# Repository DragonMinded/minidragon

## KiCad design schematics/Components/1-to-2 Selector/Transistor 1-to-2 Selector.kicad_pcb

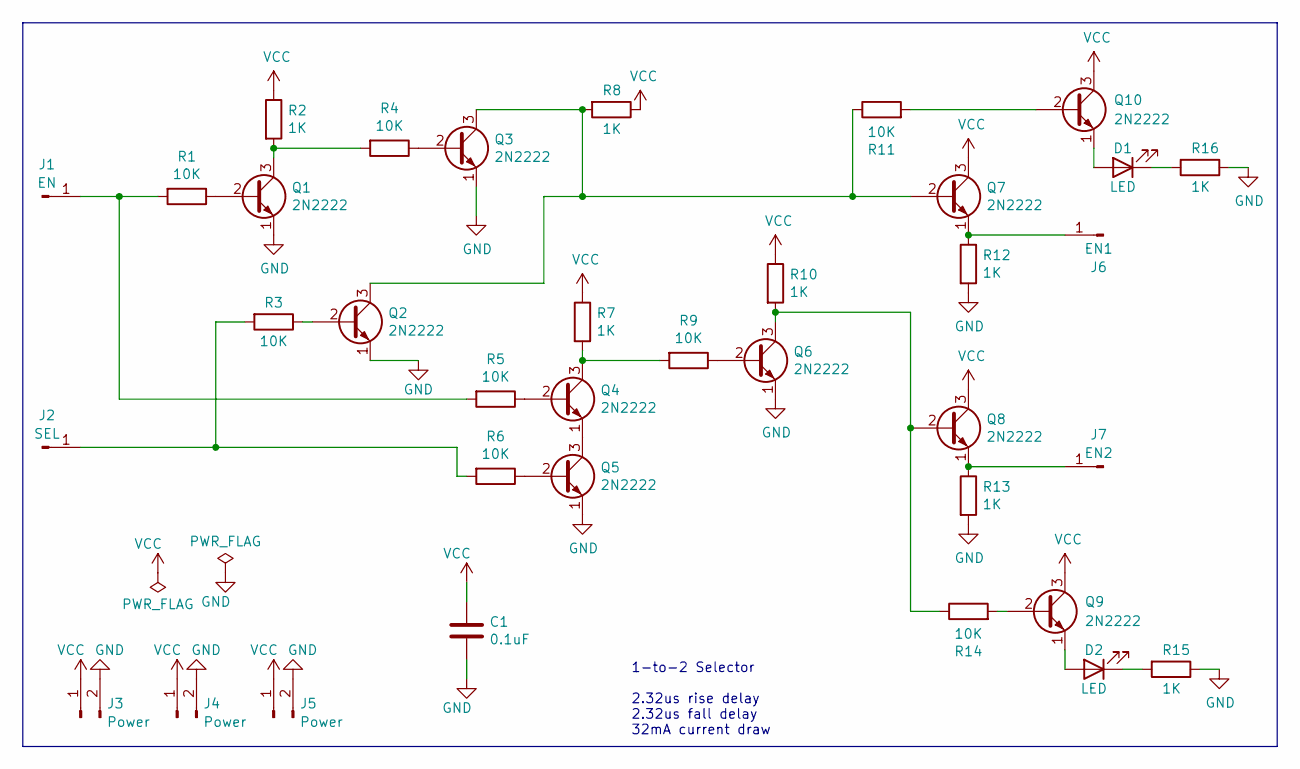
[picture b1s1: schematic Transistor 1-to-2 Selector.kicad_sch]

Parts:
C1: 0.1uF; C_Disc_D4.3mm_W1.9mm_P5.00mm
D1, D2: LED; LED_D5.0mm
J1: EN; PinHeader_1x01_P2.54mm_Vertical
J2: SEL; PinHeader_1x01_P2.54mm_Vertical
J3, J4, J5: Power; PinHeader_1x02_P2.54mm_Vertical
J6: EN1; PinHeader_1x01_P2.54mm_Vertical
J7: EN2; PinHeader_1x01_P2.54mm_Vertical
Q1, Q2, Q3, Q4, Q5, Q6, Q7, Q8, Q9, Q10: 2N2222; TO-92_Inline
R1, R3, R4, R5, R6, R9, R11, R14: 10K; R_Axial_DIN0309_L9.0mm_D3.2mm_P12.70mm_Horizontal
R2, R7, R8, R10, R12, R13, R15, R16: 1K; R_Axial_DIN0309_L9.0mm_D3.2mm_P12.70mm_Horizontal

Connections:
GND: C1.2, J3.2, J4.2, J5.2, Q1.1 (E), Q2.1 (E), Q3.1 (E), Q5.1 (E), Q6.1 (E), R12.2, R13.2, R15.1, R16.1
unnamed: D1.2 (A), Q10.1 (E)
unnamed: D1.1 (K), R16.2
unnamed: D2.2 (A), Q9.1 (E)
unnamed: D2.1 (K), R15.2
unnamed: J1.1, R1.2, R5.2
unnamed: J2.1, R3.2, R6.2
unnamed: J6.1, Q7.1 (E), R12.1
unnamed: J7.1, Q8.1 (E), R13.1
unnamed: Q1.2 (B), R1.1
unnamed: Q1.3 (C), R2.2, R4.2
unnamed: Q2.2 (B), R3.1
unnamed: Q2.3 (C), Q3.3 (C), Q7.2 (B), R8.2, R11.1
unnamed: Q3.2 (B), R4.1
unnamed: Q4.2 (B), R5.1
unnamed: Q4.3 (C), R7.2, R9.2
unnamed: Q4.1 (E), Q5.3 (C)
unnamed: Q5.2 (B), R6.1
unnamed: Q6.2 (B), R9.1
unnamed: Q6.3 (C), Q8.2 (B), R10.2, R14.1
unnamed: Q9.2 (B), R14.2
unnamed: Q10.2 (B), R11.2
VCC: C1.1, J3.1, J4.1, J5.1, Q7.3 (C), Q8.3 (C), Q9.3 (C), Q10.3 (C), R2.1, R7.1, R8.1, R10.1

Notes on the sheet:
1-to-2 Selector 2.32us rise delay 2.32us fall delay 32mA current draw

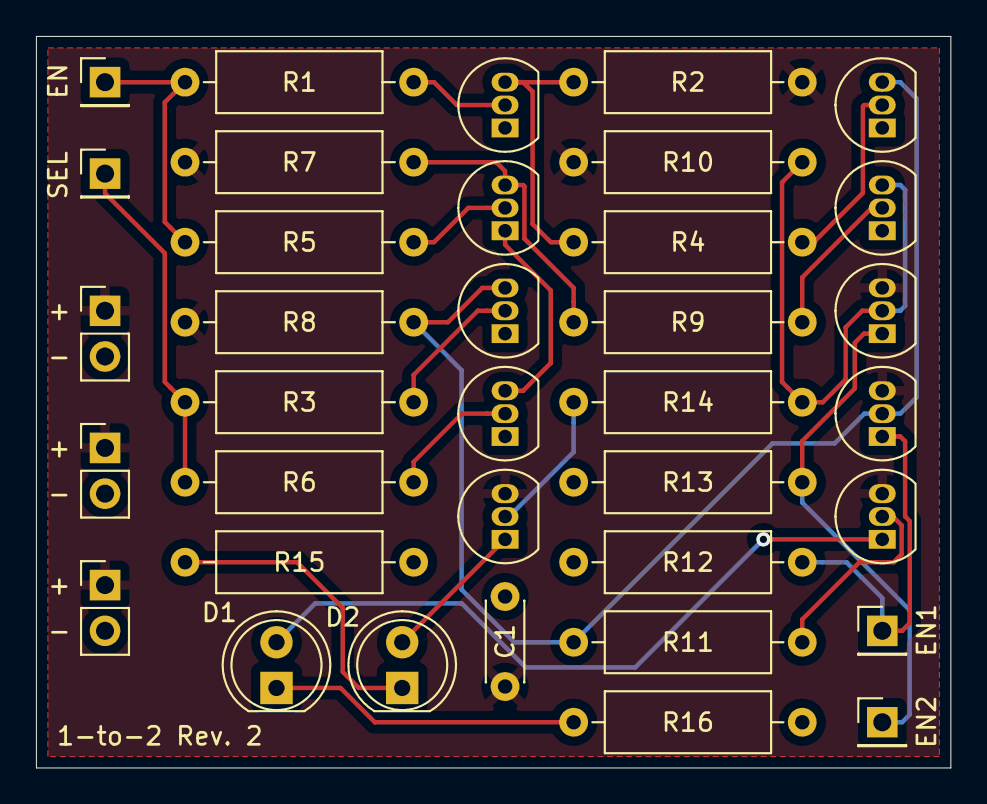
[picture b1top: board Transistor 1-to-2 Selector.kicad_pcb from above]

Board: 2 copper layers, 50.8 x 40.6 mm, 36 parts (0 on the bottom side), 23 nets.

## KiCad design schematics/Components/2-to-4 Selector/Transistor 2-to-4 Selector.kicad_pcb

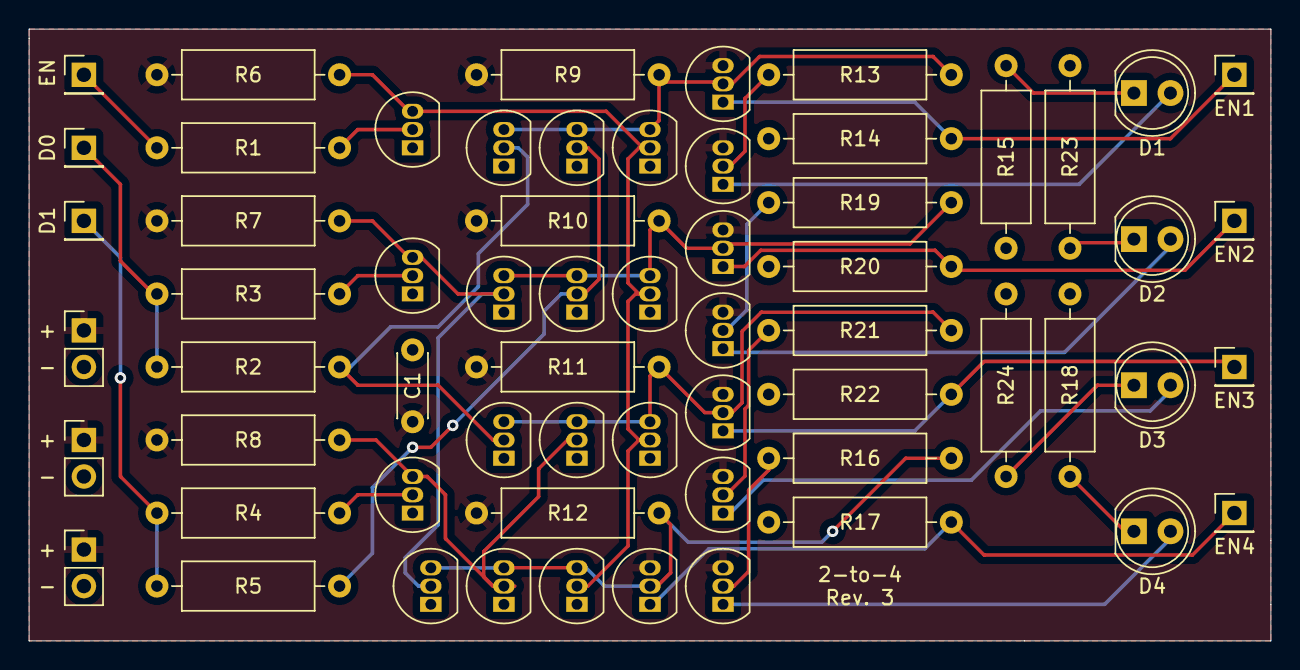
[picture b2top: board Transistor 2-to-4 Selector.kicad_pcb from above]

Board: 2 copper layers, 86.4 x 42.5 mm, 62 parts (0 on the bottom side), 33 nets.

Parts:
C1: 0.1uF; C_Disc_D4.3mm_W1.9mm_P5.00mm
D1, D2, D3, D4: LED; LED_D5.0mm
J1: EN; PinHeader_1x01_P2.54mm_Vertical
J2: D0; PinHeader_1x01_P2.54mm_Vertical
J3, J4, J5: Power; PinHeader_1x02_P2.54mm_Vertical
J6: D1; PinHeader_1x01_P2.54mm_Vertical
J7: EN1; PinHeader_1x01_P2.54mm_Vertical
J8: EN2; PinHeader_1x01_P2.54mm_Vertical
J9: EN3; PinHeader_1x01_P2.54mm_Vertical
J10: EN4; PinHeader_1x01_P2.54mm_Vertical
Q1, Q2, Q3, Q4, Q5, Q6, Q7, Q8, Q9, Q10, Q11, Q12, Q13, Q14, Q15, Q16, Q17, Q18, Q19, Q20, Q21, Q22, Q23: 2N2222; TO-92_Inline
R1, R2, R3, R4, R5, R13, R16, R19, R21: 10K; R_Axial_DIN0309_L9.0mm_D3.2mm_P12.70mm_Horizontal
R6, R7, R8, R9, R10, R11, R12, R14, R15, R17, R18, R20, R22, R23, R24: 1K; R_Axial_DIN0309_L9.0mm_D3.2mm_P12.70mm_Horizontal

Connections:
GND: C1.2, J3.2, J4.2, J5.2, Q1.1 (E), Q2.1 (E), Q3.1 (E), Q4.1 (E), Q5.1 (E), Q6.1 (E), Q7.1 (E), Q8.1 (E), Q9.1 (E), Q10.1 (E), Q11.1 (E), Q12.1 (E), Q13.1 (E), Q14.1 (E), Q15.1 (E), R14.1, R15.1, R17.1, R18.1, R20.1, R22.1, R23.1, R24.1
unnamed: D1.2 (A), Q17.1 (E)
unnamed: D1.1 (K), R15.2
unnamed: D2.2 (A), Q21.1 (E)
unnamed: D2.1 (K), R23.2
unnamed: D3.2 (A), Q23.1 (E)
unnamed: D3.1 (K), R24.2
unnamed: D4.2 (A), Q19.1 (E)
unnamed: D4.1 (K), R18.2
unnamed: J1.1, R1.2
unnamed: J2.1, R2.2, R3.2
unnamed: J6.1, R4.2, R5.2
unnamed: J7.1, Q16.1 (E), R14.2
unnamed: J8.1, Q20.1 (E), R20.2
unnamed: J9.1, Q22.1 (E), R22.2
unnamed: J10.1, Q18.1 (E), R17.2
unnamed: Q1.2 (B), R1.1
unnamed: Q1.3 (C), Q12.2 (B), Q13.2 (B), Q14.2 (B), Q15.2 (B), R6.2
unnamed: Q2.2 (B), R3.1
unnamed: Q2.3 (C), Q5.2 (B), Q7.2 (B), R7.2
unnamed: Q3.2 (B), R4.1
unnamed: Q4.2 (B), Q6.2 (B), R2.1
unnamed: Q8.2 (B), Q9.2 (B), R5.1
unnamed: Q3.3 (C), Q10.2 (B), Q11.2 (B), R8.2
unnamed: Q6.3 (C), Q10.3 (C), Q14.3 (C), Q22.2 (B), R11.2, R21.2
unnamed: Q7.3 (C), Q11.3 (C), Q15.3 (C), Q18.2 (B), R12.2, R16.2
unnamed: Q4.3 (C), Q8.3 (C), Q12.3 (C), Q16.2 (B), R9.2, R13.2
unnamed: Q5.3 (C), Q9.3 (C), Q13.3 (C), Q20.2 (B), R10.2, R19.2
unnamed: Q17.2 (B), R13.1
unnamed: Q19.2 (B), R16.1
unnamed: Q21.2 (B), R19.1
unnamed: Q23.2 (B), R21.1
VCC: C1.1, J3.1, J4.1, J5.1, Q16.3 (C), Q17.3 (C), Q18.3 (C), Q19.3 (C), Q20.3 (C), Q21.3 (C), Q22.3 (C), Q23.3 (C), R6.1, R7.1, R8.1, R9.1, R10.1, R11.1, R12.1

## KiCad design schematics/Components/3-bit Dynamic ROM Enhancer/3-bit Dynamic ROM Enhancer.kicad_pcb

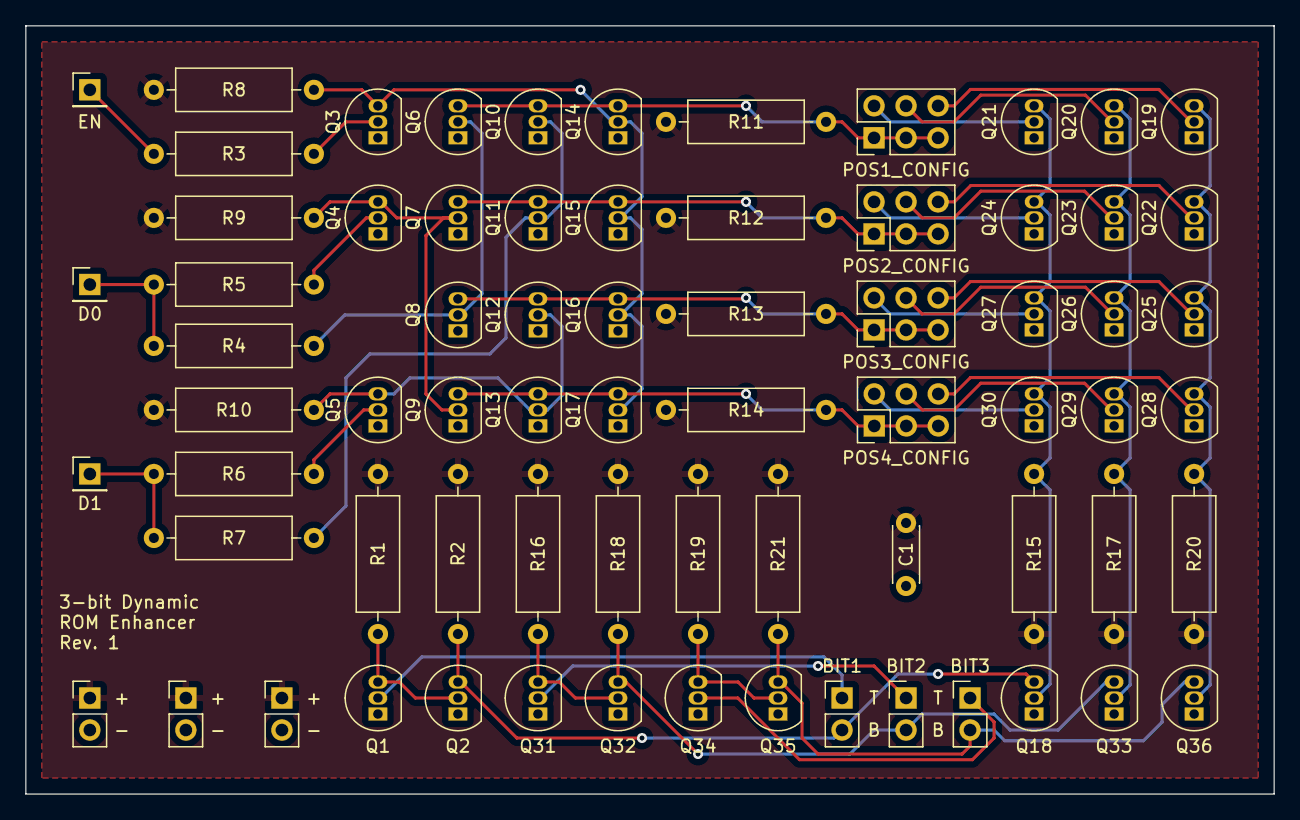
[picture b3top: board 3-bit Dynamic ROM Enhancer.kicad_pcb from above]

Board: 2 copper layers, 99.1 x 61.0 mm, 71 parts (0 on the bottom side), 41 nets.

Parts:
C1: 0.1uF; C_Disc_D4.3mm_W1.9mm_P5.00mm
J1, J2, J3: POWER; PinHeader_1x02_P2.54mm_Vertical
J4: BIT1; PinHeader_1x02_P2.54mm_Vertical
J5: BIT2; PinHeader_1x02_P2.54mm_Vertical
J6: BIT3; PinHeader_1x02_P2.54mm_Vertical
J7: EN; PinHeader_1x01_P2.54mm_Vertical
J8: D0; PinHeader_1x01_P2.54mm_Vertical
J9: D1; PinHeader_1x01_P2.54mm_Vertical
J10: POS1_CONFIG; PinHeader_2x03_P2.54mm_Vertical
J11: POS2_CONFIG; PinHeader_2x03_P2.54mm_Vertical
J12: POS3_CONFIG; PinHeader_2x03_P2.54mm_Vertical
J13: POS4_CONFIG; PinHeader_2x03_P2.54mm_Vertical
Q1, Q2, Q3, Q4, Q5, Q6, Q7, Q8, Q9, Q10, Q11, Q12, Q13, Q14, Q15, Q16, Q17, Q18, Q19, Q20, Q21, Q22, Q23, Q24, Q25, Q26, Q27, Q28, Q29, Q30, Q31, Q32, Q33, Q34, Q35, Q36: 2N2222; TO-92_Inline
R1, R2, R8, R9, R10, R15, R16, R17, R18, R19, R20, R21: 1K; R_Axial_DIN0309_L9.0mm_D3.2mm_P12.70mm_Horizontal
R3, R4, R5, R6, R7, R11, R12, R13, R14: 10K; R_Axial_DIN0309_L9.0mm_D3.2mm_P12.70mm_Horizontal

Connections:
/BIT1_EN: Q18.2 (B), Q21.3 (C), Q24.3 (C), Q27.3 (C), Q30.3 (C), R15.1
/BIT1_IN: J4.1, Q1.2 (B)
/BIT1_OUT: J4.2, Q2.3 (C), Q18.3 (C), R2.1
/BIT2_EN: Q20.3 (C), Q23.3 (C), Q26.3 (C), Q29.3 (C), Q33.2 (B), R17.1
/BIT2_IN: J5.1, Q31.2 (B)
/BIT2_OUT: J5.2, Q32.3 (C), Q33.3 (C), R18.1
/BIT3_EN: Q19.3 (C), Q22.3 (C), Q25.3 (C), Q28.3 (C), Q36.2 (B), R20.1
/BIT3_IN: J6.1, Q34.2 (B)
/BIT3_OUT: J6.2, Q35.3 (C), Q36.3 (C), R21.1
GND: C1.2, J1.2, J2.2, J3.2, Q1.1 (E), Q2.1 (E), Q3.1 (E), Q4.1 (E), Q5.1 (E), Q6.1 (E), Q7.1 (E), Q8.1 (E), Q9.1 (E), Q10.1 (E), Q11.1 (E), Q12.1 (E), Q13.1 (E), Q14.1 (E), Q15.1 (E), Q16.1 (E), Q17.1 (E), Q18.1 (E), Q19.1 (E), Q20.1 (E), Q21.1 (E), Q22.1 (E), Q23.1 (E), Q24.1 (E), Q25.1 (E), Q26.1 (E), Q27.1 (E), Q28.1 (E), Q29.1 (E), Q30.1 (E), Q31.1 (E), Q32.1 (E), Q33.1 (E), Q34.1 (E), Q35.1 (E), Q36.1 (E)
unnamed: J7.1, R3.2
unnamed: J8.1, R4.2, R5.2
unnamed: J9.1, R6.2, R7.2
unnamed: J10.1, J10.3, J10.5, Q6.3 (C), Q10.3 (C), Q14.3 (C), R11.2
unnamed: J10.2, Q21.2 (B)
unnamed: J10.4, Q20.2 (B)
unnamed: J10.6, Q19.2 (B)
unnamed: J11.1, J11.3, J11.5, Q7.3 (C), Q11.3 (C), Q15.3 (C), R12.2
unnamed: J11.2, Q24.2 (B)
unnamed: J11.4, Q23.2 (B)
unnamed: J11.6, Q22.2 (B)
unnamed: J12.1, J12.3, J12.5, Q8.3 (C), Q12.3 (C), Q16.3 (C), R13.2
unnamed: J12.2, Q27.2 (B)
unnamed: J12.4, Q26.2 (B)
unnamed: J12.6, Q25.2 (B)
unnamed: J13.1, J13.3, J13.5, Q9.3 (C), Q13.3 (C), Q17.3 (C), R14.2
unnamed: J13.2, Q30.2 (B)
unnamed: J13.4, Q29.2 (B)
unnamed: J13.6, Q28.2 (B)
unnamed: Q1.3 (C), Q2.2 (B), R1.1
unnamed: Q3.2 (B), R3.1
unnamed: Q4.2 (B), R5.1
unnamed: Q4.3 (C), Q7.2 (B), Q9.2 (B), R9.2
unnamed: Q5.2 (B), R6.1
unnamed: Q6.2 (B), Q8.2 (B), R4.1
unnamed: Q10.2 (B), Q11.2 (B), R7.1
unnamed: Q5.3 (C), Q12.2 (B), Q13.2 (B), R10.2
unnamed: Q3.3 (C), Q14.2 (B), Q15.2 (B), Q16.2 (B), Q17.2 (B), R8.2
unnamed: Q31.3 (C), Q32.2 (B), R16.1
unnamed: Q34.3 (C), Q35.2 (B), R19.1
VCC: C1.1, J1.1, J2.1, J3.1, R1.2, R2.2, R8.1, R9.1, R10.1, R11.1, R12.1, R13.1, R14.1, R15.2, R16.2, R17.2, R18.2, R19.2, R20.2, R21.2

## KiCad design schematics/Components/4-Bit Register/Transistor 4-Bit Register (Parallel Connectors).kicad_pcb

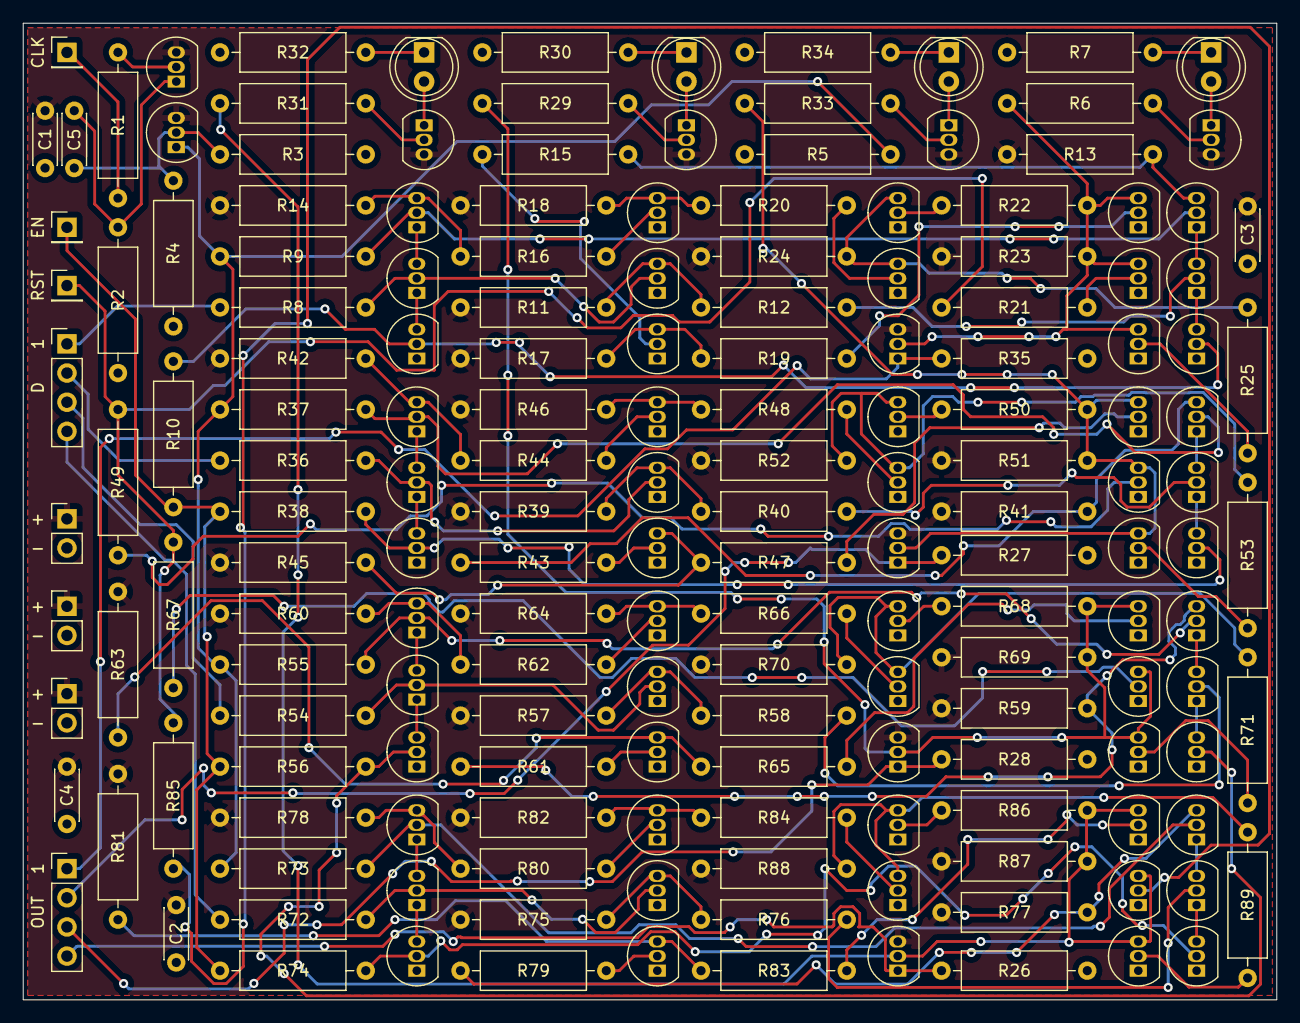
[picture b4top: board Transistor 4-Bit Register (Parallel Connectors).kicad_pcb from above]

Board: 2 copper layers, 109.2 x 85.1 mm, 172 parts (0 on the bottom side), 117 nets.

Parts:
C1, C2, C3, C4, C5: 0.1uF; C_Disc_D4.3mm_W1.9mm_P5.00mm
CLK: CLK; PinHeader_1x01_P2.54mm_Vertical
D: D; PinHeader_1x04_P2.54mm_Vertical
D1, D2, D3, D4: LED; LED_D5.0mm
EN: EN; PinHeader_1x01_P2.54mm_Vertical
J6, J7, J8: Power; PinHeader_1x02_P2.54mm_Vertical
OUT: OUT; PinHeader_1x04_P2.54mm_Vertical
Q1, Q2, Q4, Q5, Q6, Q7, Q8, Q9, Q10, Q11, Q12, Q13, Q14, Q15, Q16, Q17, Q18, Q19, Q20, Q21, Q22, Q23, Q24, Q25, Q26, Q27, Q28, Q29, Q30, Q31, Q32, Q33, Q34, Q35, Q36, Q37, Q38, Q39, Q40, Q41, Q42, Q43, Q44, Q45, Q46, Q47, Q48, Q49, Q50, Q51, Q52, Q53, Q54, Q55, Q56, Q57, Q58, Q59, Q60, Q61, Q62, Q63, Q64, Q65, Q66, Q67: 2N2222; TO-92_Inline
R1, R5, R7, R11, R13, R14, R17, R18, R23, R24, R26, R27, R28, R30, R32, R34, R35, R39, R41, R42, R45, R46, R51, R52, R57, R59, R60, R63, R64, R69, R70, R75, R77, R78, R81, R82, R87, R88: 1K; R_Axial_DIN0309_L9.0mm_D3.2mm_P12.70mm_Horizontal
R2, R3, R4: 100; R_Axial_DIN0309_L9.0mm_D3.2mm_P12.70mm_Horizontal
R6, R8, R9, R10, R12, R15, R16, R19, R20, R21, R22, R25, R29, R31, R33, R36, R37, R38, R40, R43, R44, R47, R48, R49, R50, R53, R54, R55, R56, R58, R61, R62, R65, R66, R67, R68, R71, R72, R73, R74, R76, R79, R80, R83, R84, R85, R86, R89: 10K; R_Axial_DIN0309_L9.0mm_D3.2mm_P12.70mm_Horizontal
RST: RST; PinHeader_1x01_P2.54mm_Vertical

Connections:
/Buffer Out Bit 1/BufOut: OUT.1, Q25.1, R35.2
/Buffer Out Bit 1/D: Q14.3, Q16.3, Q18.3, Q25.2, R6.2, R22.1, R23.1
/Buffer Out Bit 2/BufOut: OUT.2, Q20.1, R27.2
/Buffer Out Bit 2/D: Q20.2, Q35.3, Q37.3, Q39.3, R33.2, R50.1, R51.1
/Buffer Out Bit 3/BufOut: OUT.3, Q21.1, R28.2
/Buffer Out Bit 3/D: Q21.2, Q49.3, Q51.3, Q53.3, R29.2, R68.1, R69.1
/Buffer Out Bit 4/BufOut: OUT.4, Q19.1, R26.2
/Buffer Out Bit 4/D: Q19.2, Q63.3, Q65.3, Q67.3, R31.2, R86.1, R87.1
/Clock Edge Detection/ClkIn: CLK.1, R1.2
/D Flip Flop Bit 1/D: D.1, R8.2
/D Flip Flop Bit 1/EN1: Q2.1, R5.1, R9.2, R37.2, R55.2, R73.2
/D Flip Flop Bit 1/EN2: EN.1, R10.2, R38.2, R56.2, R74.2
/D Flip Flop Bit 1/RST: R21.2, R49.2, R67.2, R85.2, RST.1
/D Flip Flop Bit 2/D: D.2, R36.2
/D Flip Flop Bit 3/D: D.3, R54.2
/D Flip Flop Bit 4/D: D.4, R72.2
GND: C1.1, C2.1, C3.1, C4.1, J6.2, J7.2, J8.2, Q5.1, Q10.1, Q11.1, Q12.1, Q13.1, Q14.1, Q15.1, Q16.1, Q17.1, Q18.1, Q26.1, Q31.1, Q32.1, Q33.1, Q34.1, Q35.1, Q36.1, Q37.1, Q38.1, Q39.1, Q40.1, Q45.1, Q46.1, Q47.1, Q48.1, Q49.1, Q50.1, Q51.1, Q52.1, Q53.1, Q54.1, Q59.1, Q60.1, Q61.1, Q62.1, Q63.1, Q64.1, Q65.1, Q66.1, Q67.1, R2.2, R3.2, R4.2, R5.2, R7.1, R26.1, R27.1, R28.1, R30.1, R32.1, R34.1, R35.1
unnamed: C5.1, Q1.1, R2.1
unnamed: C5.2, Q2.2, R3.1, R4.1
unnamed: D1.1, R7.2
unnamed: D1.2, Q4.1
unnamed: D2.1, R30.2
unnamed: D2.2, Q22.1
unnamed: D3.1, R32.2
unnamed: D3.2, Q23.1
unnamed: D4.1, R34.2
unnamed: D4.2, Q24.1
unnamed: Q1.2, R1.1
unnamed: Q4.2, R6.1
unnamed: Q5.2, Q9.2, R8.1
unnamed: Q5.3, R11.2, R12.2
unnamed: Q6.1, Q7.3
unnamed: Q6.2, Q8.2, R9.1
unnamed: Q6.3, R13.2, R15.2
unnamed: Q7.2, R12.1
unnamed: Q8.1, Q9.3
unnamed: Q8.3, R14.2, R16.2
unnamed: Q10.2, Q11.2, R10.1
unnamed: Q9.1, Q10.3
unnamed: Q7.1, Q11.3
unnamed: Q12.2, R15.1
unnamed: Q12.3, R17.2, R19.2
unnamed: Q13.2, R16.1
unnamed: Q13.3, R18.2, R20.2
unnamed: Q14.2, R19.1
unnamed: Q15.2, R20.1
unnamed: Q15.3, Q17.3, R24.2, R25.2
unnamed: Q16.2, R21.1
unnamed: Q17.2, R22.2
unnamed: Q18.2, R25.1
unnamed: Q22.2, R29.1
unnamed: Q23.2, R31.1
unnamed: Q24.2, R33.1
unnamed: Q26.2, Q30.2, R36.1
unnamed: Q26.3, R39.2, R40.2
unnamed: Q27.1, Q28.3
unnamed: Q27.2, Q29.2, R37.1
unnamed: Q27.3, R41.2, R43.2
unnamed: Q28.1, Q32.3
unnamed: Q28.2, R40.1
unnamed: Q29.1, Q30.3
unnamed: Q29.3, R42.2, R44.2
unnamed: Q30.1, Q31.3
unnamed: Q31.2, Q32.2, R38.1
unnamed: Q33.2, R43.1
unnamed: Q33.3, R45.2, R47.2
unnamed: Q34.2, R44.1
unnamed: Q34.3, R46.2, R48.2
unnamed: Q35.2, R47.1
unnamed: Q36.2, R48.1
unnamed: Q36.3, Q38.3, R52.2, R53.2
unnamed: Q37.2, R49.1
unnamed: Q38.2, R50.2
unnamed: Q39.2, R53.1
unnamed: Q40.2, Q44.2, R54.1
unnamed: Q40.3, R57.2, R58.2
unnamed: Q41.1, Q42.3
unnamed: Q41.2, Q43.2, R55.1
unnamed: Q41.3, R59.2, R61.2
unnamed: Q42.1, Q46.3
unnamed: Q42.2, R58.1
unnamed: Q43.1, Q44.3
unnamed: Q43.3, R60.2, R62.2
unnamed: Q44.1, Q45.3
unnamed: Q45.2, Q46.2, R56.1
unnamed: Q47.2, R61.1
unnamed: Q47.3, R63.2, R65.2
unnamed: Q48.2, R62.1
unnamed: Q48.3, R64.2, R66.2
unnamed: Q49.2, R65.1
unnamed: Q50.2, R66.1
unnamed: Q50.3, Q52.3, R70.2, R71.2
unnamed: Q51.2, R67.1
unnamed: Q52.2, R68.2
unnamed: Q53.2, R71.1
unnamed: Q54.2, Q58.2, R72.1
unnamed: Q54.3, R75.2, R76.2
unnamed: Q55.1, Q56.3
unnamed: Q55.2, Q57.2, R73.1
unnamed: Q55.3, R77.2, R79.2
unnamed: Q56.1, Q60.3
unnamed: Q56.2, R76.1
unnamed: Q57.1, Q58.3
unnamed: Q57.3, R78.2, R80.2
unnamed: Q58.1, Q59.3
unnamed: Q59.2, Q60.2, R74.1
unnamed: Q61.2, R79.1
unnamed: Q61.3, R81.2, R83.2
unnamed: Q62.2, R80.1
unnamed: Q62.3, R82.2, R84.2
unnamed: Q63.2, R83.1
unnamed: Q64.2, R84.1
unnamed: Q64.3, Q66.3, R88.2, R89.2
unnamed: Q65.2, R85.1
unnamed: Q66.2, R86.2
unnamed: Q67.2, R89.1
VCC: C1.2, C2.2, C3.2, C4.2, J6.1, J7.1, J8.1, Q1.3, Q2.3, Q4.3, Q19.3, Q20.3, Q21.3, Q22.3, Q23.3, Q24.3, Q25.3, R11.1, R13.1, R14.1, R17.1, R18.1, R23.2, R24.1, R39.1, R41.1, R42.1, R45.1, R46.1, R51.2, R52.1, R57.1, R59.1, R60.1, R63.1, R64.1, R69.2, R70.1, R75.1, R77.1, R78.1, R81.1, R82.1, R87.2, R88.1

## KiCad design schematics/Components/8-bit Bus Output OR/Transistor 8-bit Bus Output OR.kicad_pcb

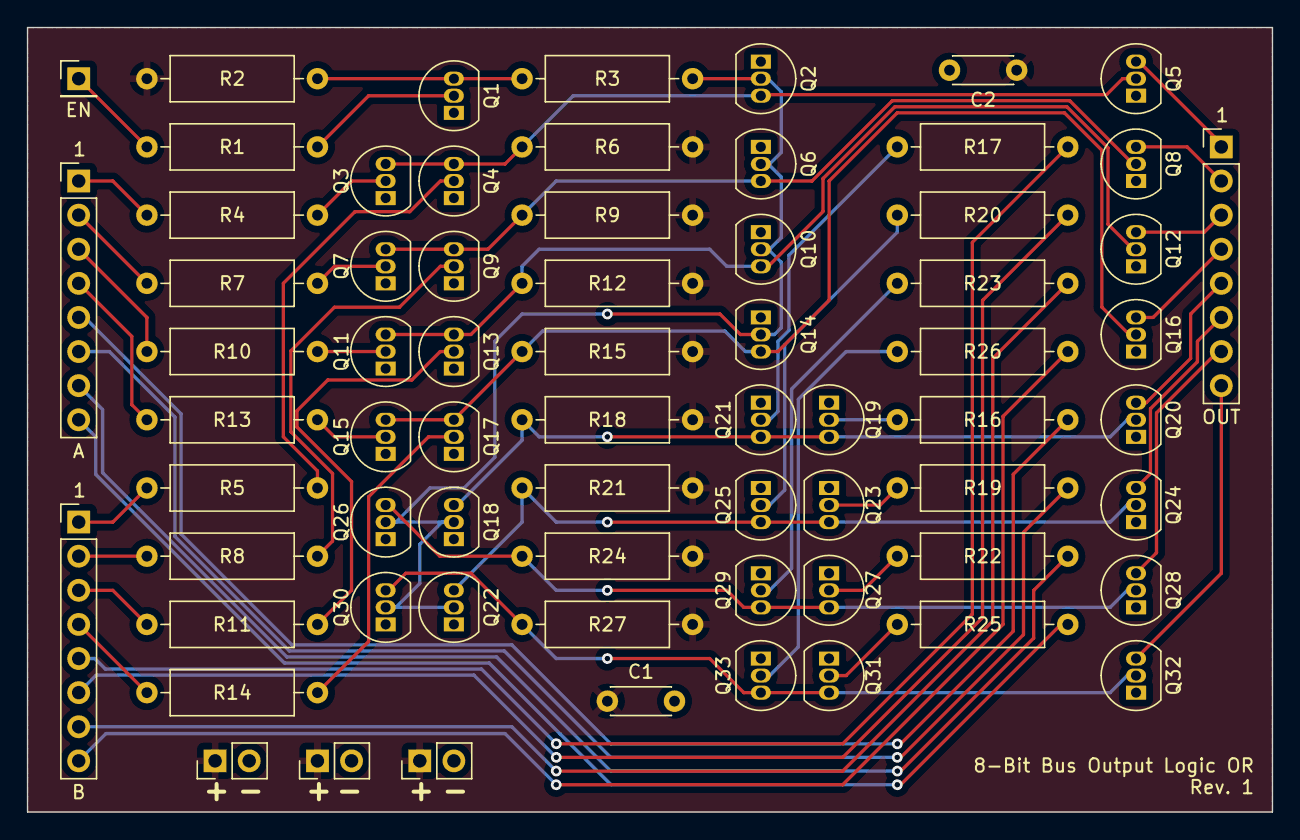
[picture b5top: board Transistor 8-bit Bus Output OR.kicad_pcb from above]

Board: 2 copper layers, 92.7 x 58.4 mm, 69 parts (0 on the bottom side), 54 nets.

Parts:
C1, C2: 0.1uF; C_Disc_D4.3mm_W1.9mm_P5.00mm
J1: EN; PinHeader_1x01_P2.54mm_Vertical
J2: A; PinHeader_1x08_P2.54mm_Vertical
J3: B; PinHeader_1x08_P2.54mm_Vertical
J4: OUT; PinHeader_1x08_P2.54mm_Vertical
J5, J6, J7: POWER; PinHeader_1x02_P2.54mm_Vertical
Q1, Q2, Q3, Q4, Q5, Q6, Q7, Q8, Q9, Q10, Q11, Q12, Q13, Q14, Q15, Q16, Q17, Q18, Q19, Q20, Q21, Q22, Q23, Q24, Q25, Q26, Q27, Q28, Q29, Q30, Q31, Q32, Q33: 2N2222; TO-92_Inline
R1, R4, R5, R7, R8, R10, R11, R13, R14, R16, R17, R19, R20, R22, R23, R25, R26: 10K; R_Axial_DIN0309_L9.0mm_D3.2mm_P12.70mm_Horizontal
R2, R6, R9, R12, R15, R18, R21, R24, R27: 1K; R_Axial_DIN0309_L9.0mm_D3.2mm_P12.70mm_Horizontal
R3: 100; R_Axial_DIN0309_L9.0mm_D3.2mm_P12.70mm_Horizontal

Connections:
/A1: J2.1, R4.2
/A2: J2.2, R7.2
/A3: J2.3, R10.2
/A4: J2.4, R13.2
/A5: J2.5, R16.2
/A6: J2.6, R19.2
/A7: J2.7, R22.2
/A8: J2.8, R25.2
/B1: J3.1, R5.2
/B2: J3.2, R8.2
/B3: J3.3, R11.2
/B4: J3.4, R14.2
/B5: J3.5, R17.2
/B6: J3.6, R20.2
/B7: J3.7, R23.2
/B8: J3.8, R26.2
/EN_INT: Q2.2 (B), Q6.2 (B), Q10.2 (B), Q14.2 (B), Q18.2 (B), Q22.2 (B), Q26.2 (B), Q30.2 (B), R3.1
/O1: J4.1, Q5.3 (C)
/O2: J4.2, Q8.3 (C)
/O3: J4.3, Q12.3 (C)
/O4: J4.4, Q16.3 (C)
/O5: J4.5, Q20.3 (C)
/O6: J4.6, Q24.3 (C)
/O7: J4.7, Q28.3 (C)
/O8: J4.8, Q32.3 (C)
GND: C1.2, C2.2, J5.2, J6.2, J7.2, Q1.1 (E), Q2.1 (E), Q3.1 (E), Q4.1 (E), Q5.1 (E), Q6.1 (E), Q7.1 (E), Q8.1 (E), Q9.1 (E), Q10.1 (E), Q11.1 (E), Q12.1 (E), Q13.1 (E), Q14.1 (E), Q15.1 (E), Q16.1 (E), Q17.1 (E), Q18.1 (E), Q19.1 (E), Q20.1 (E), Q21.1 (E), Q22.1 (E), Q23.1 (E), Q24.1 (E), Q25.1 (E), Q26.1 (E), Q27.1 (E), Q28.1 (E), Q29.1 (E), Q30.1 (E), Q31.1 (E), Q32.1 (E), Q33.1 (E)
unnamed: J1.1, R1.2
unnamed: Q1.2 (B), R1.1
unnamed: Q1.3 (C), R2.1, R3.2
unnamed: Q2.3 (C), Q3.3 (C), Q4.3 (C), Q5.2 (B), R6.1
unnamed: Q3.2 (B), R4.1
unnamed: Q4.2 (B), R5.1
unnamed: Q6.3 (C), Q7.3 (C), Q8.2 (B), Q9.3 (C), R9.1
unnamed: Q7.2 (B), R7.1
unnamed: Q9.2 (B), R8.1
unnamed: Q10.3 (C), Q11.3 (C), Q12.2 (B), Q13.3 (C), R12.1
unnamed: Q11.2 (B), R10.1
unnamed: Q13.2 (B), R11.1
unnamed: Q14.3 (C), Q15.3 (C), Q16.2 (B), Q17.3 (C), R15.1
unnamed: Q15.2 (B), R13.1
unnamed: Q17.2 (B), R14.1
unnamed: Q18.3 (C), Q19.3 (C), Q20.2 (B), Q21.3 (C), R18.1
unnamed: Q19.2 (B), R16.1
unnamed: Q21.2 (B), R17.1
unnamed: Q22.3 (C), Q23.3 (C), Q24.2 (B), Q25.3 (C), R21.1
unnamed: Q23.2 (B), R19.1
unnamed: Q25.2 (B), R20.1
unnamed: Q26.3 (C), Q27.3 (C), Q28.2 (B), Q29.3 (C), R24.1
unnamed: Q27.2 (B), R22.1
unnamed: Q29.2 (B), R23.1
unnamed: Q30.3 (C), Q31.3 (C), Q32.2 (B), Q33.3 (C), R27.1
unnamed: Q31.2 (B), R25.1
unnamed: Q33.2 (B), R26.1
VCC: C1.1, C2.1, J5.1, J6.1, J7.1, R2.2, R6.2, R9.2, R12.2, R15.2, R18.2, R21.2, R24.2, R27.2

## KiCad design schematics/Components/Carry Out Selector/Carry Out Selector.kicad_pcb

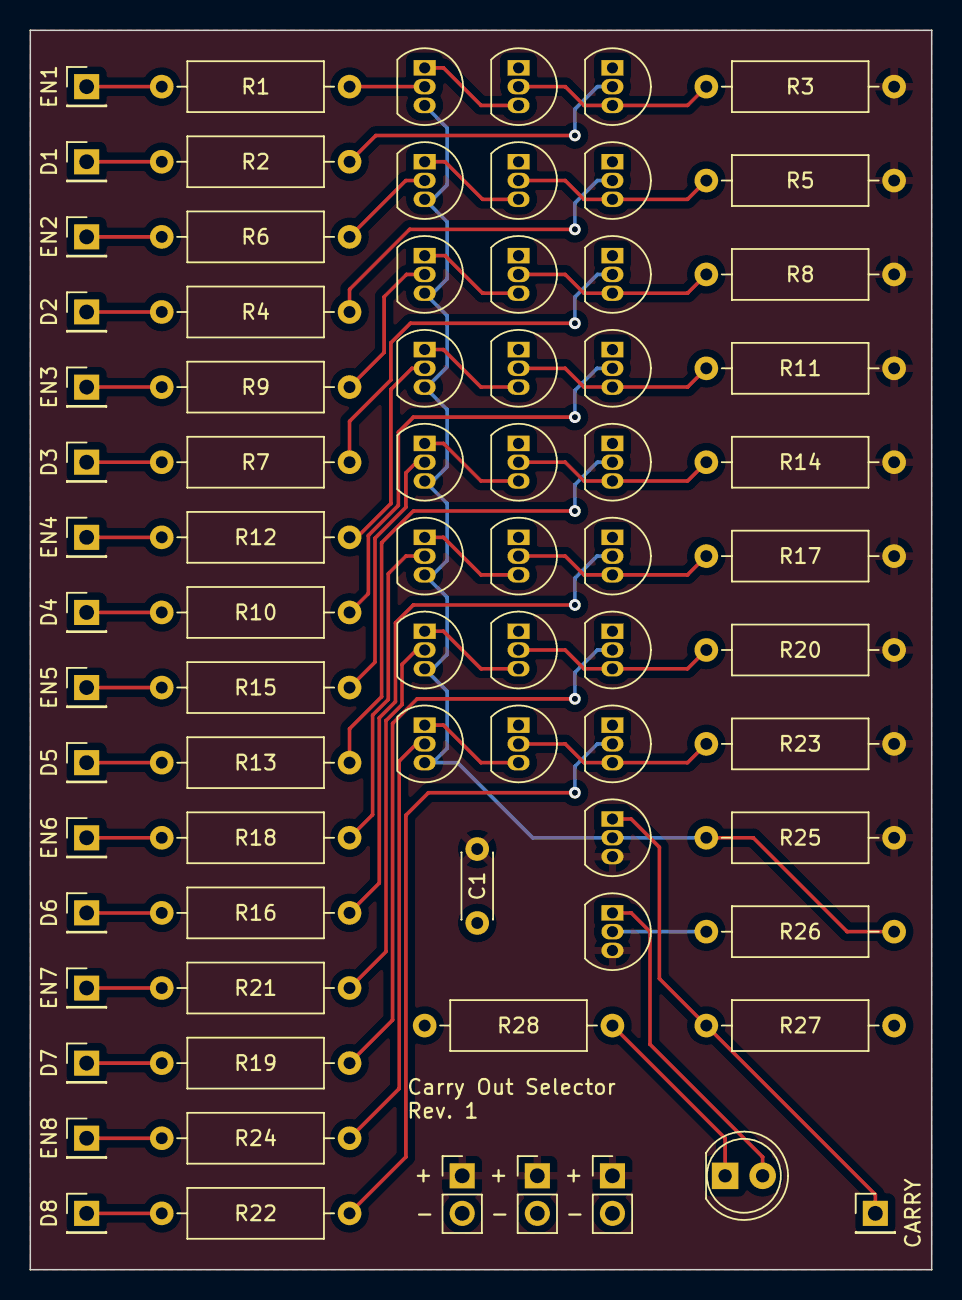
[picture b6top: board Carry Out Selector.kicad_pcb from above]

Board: 2 copper layers, 61.0 x 83.8 mm, 76 parts (0 on the bottom side), 55 nets.

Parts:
C1: 0.1uF; C_Disc_D4.3mm_W1.9mm_P5.00mm
D1: LED; LED_D5.0mm
J1, J2, J3: POWER; PinHeader_1x02_P2.54mm_Vertical
J4: D1; PinHeader_1x01_P2.54mm_Vertical
J5: EN1; PinHeader_1x01_P2.54mm_Vertical
J6: D2; PinHeader_1x01_P2.54mm_Vertical
J7: EN2; PinHeader_1x01_P2.54mm_Vertical
J8: D3; PinHeader_1x01_P2.54mm_Vertical
J9: EN3; PinHeader_1x01_P2.54mm_Vertical
J10: D4; PinHeader_1x01_P2.54mm_Vertical
J11: EN4; PinHeader_1x01_P2.54mm_Vertical
J12: D5; PinHeader_1x01_P2.54mm_Vertical
J13: EN5; PinHeader_1x01_P2.54mm_Vertical
J14: D6; PinHeader_1x01_P2.54mm_Vertical
J15: EN6; PinHeader_1x01_P2.54mm_Vertical
J16: D7; PinHeader_1x01_P2.54mm_Vertical
J17: EN7; PinHeader_1x01_P2.54mm_Vertical
J18: D8; PinHeader_1x01_P2.54mm_Vertical
J19: EN8; PinHeader_1x01_P2.54mm_Vertical
J20: CARRY; PinHeader_1x01_P2.54mm_Vertical
Q1, Q2, Q3, Q4, Q5, Q6, Q7, Q8, Q9, Q10, Q11, Q12, Q13, Q14, Q15, Q16, Q17, Q18, Q19, Q20, Q21, Q22, Q23, Q24, Q25, Q26: 2N2222; TO-92_Inline
R1, R2, R4, R6, R7, R9, R10, R12, R13, R15, R16, R18, R19, R21, R22, R24, R26: 10K; R_Axial_DIN0309_L9.0mm_D3.2mm_P12.70mm_Horizontal
R3, R5, R8, R11, R14, R17, R20, R23, R25, R27, R28: 1K; R_Axial_DIN0309_L9.0mm_D3.2mm_P12.70mm_Horizontal

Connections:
/COMB_BUS: Q1.3 (C), Q5.3 (C), Q8.3 (C), Q11.3 (C), Q14.3 (C), Q17.3 (C), Q20.3 (C), Q23.3 (C), Q25.2 (B), R25.1, R26.2
GND: C1.2, J1.2, J2.2, J3.2, Q2.1 (E), Q3.1 (E), Q4.1 (E), Q6.1 (E), Q7.1 (E), Q9.1 (E), Q10.1 (E), Q12.1 (E), Q13.1 (E), Q15.1 (E), Q16.1 (E), Q18.1 (E), Q19.1 (E), Q21.1 (E), Q22.1 (E), Q24.1 (E), R27.1, R28.1
unnamed: D1.2 (A), Q26.1 (E)
unnamed: D1.1 (K), R28.2
unnamed: J4.1, R2.2
unnamed: J5.1, R1.2
unnamed: J6.1, R4.2
unnamed: J7.1, R6.2
unnamed: J8.1, R7.2
unnamed: J9.1, R9.2
unnamed: J10.1, R10.2
unnamed: J11.1, R12.2
unnamed: J12.1, R13.2
unnamed: J13.1, R15.2
unnamed: J14.1, R16.2
unnamed: J15.1, R18.2
unnamed: J16.1, R19.2
unnamed: J17.1, R21.2
unnamed: J18.1, R22.2
unnamed: J19.1, R24.2
unnamed: J20.1, Q25.1 (E), R27.2
unnamed: Q1.2 (B), R1.1
unnamed: Q1.1 (E), Q2.3 (C)
unnamed: Q2.2 (B), Q3.3 (C), R3.1
unnamed: Q3.2 (B), R2.1
unnamed: Q4.2 (B), R4.1
unnamed: Q4.3 (C), Q6.2 (B), R5.1
unnamed: Q5.2 (B), R6.1
unnamed: Q5.1 (E), Q6.3 (C)
unnamed: Q7.2 (B), R7.1
unnamed: Q7.3 (C), Q9.2 (B), R8.1
unnamed: Q8.2 (B), R9.1
unnamed: Q8.1 (E), Q9.3 (C)
unnamed: Q10.2 (B), R10.1
unnamed: Q10.3 (C), Q12.2 (B), R11.1
unnamed: Q11.2 (B), R12.1
unnamed: Q11.1 (E), Q12.3 (C)
unnamed: Q13.2 (B), R13.1
unnamed: Q13.3 (C), Q15.2 (B), R14.1
unnamed: Q14.2 (B), R15.1
unnamed: Q14.1 (E), Q15.3 (C)
unnamed: Q16.2 (B), R16.1
unnamed: Q16.3 (C), Q18.2 (B), R17.1
unnamed: Q17.2 (B), R18.1
unnamed: Q17.1 (E), Q18.3 (C)
unnamed: Q19.2 (B), R19.1
unnamed: Q19.3 (C), Q21.2 (B), R20.1
unnamed: Q20.2 (B), R21.1
unnamed: Q20.1 (E), Q21.3 (C)
unnamed: Q22.2 (B), R22.1
unnamed: Q22.3 (C), Q24.2 (B), R23.1
unnamed: Q23.2 (B), R24.1
unnamed: Q23.1 (E), Q24.3 (C)
unnamed: Q26.2 (B), R26.1
VCC: C1.1, J1.1, J2.1, J3.1, Q25.3 (C), Q26.3 (C), R3.2, R5.2, R8.2, R11.2, R14.2, R17.2, R20.2, R23.2, R25.2
